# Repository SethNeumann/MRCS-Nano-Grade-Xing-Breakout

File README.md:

# REPO NAME: MRCS-Nano-Grade-Xing-Breakout

## License: Creative Commons Attribution-NonCommercial-ShareAlike

There are plenty of good Arduino Grade Xing sketches. This board supports one by Jon Schmidt which uses the Nano's 8
analog inputs to monitor up 4 sets of sensors. It drives 2 servos for the crossing gates, 2 phases of LEDs
for the flashing lights and an output to drive a crossing bell sound module, like the ones from our friends
at Iowa Scaled Engineering.

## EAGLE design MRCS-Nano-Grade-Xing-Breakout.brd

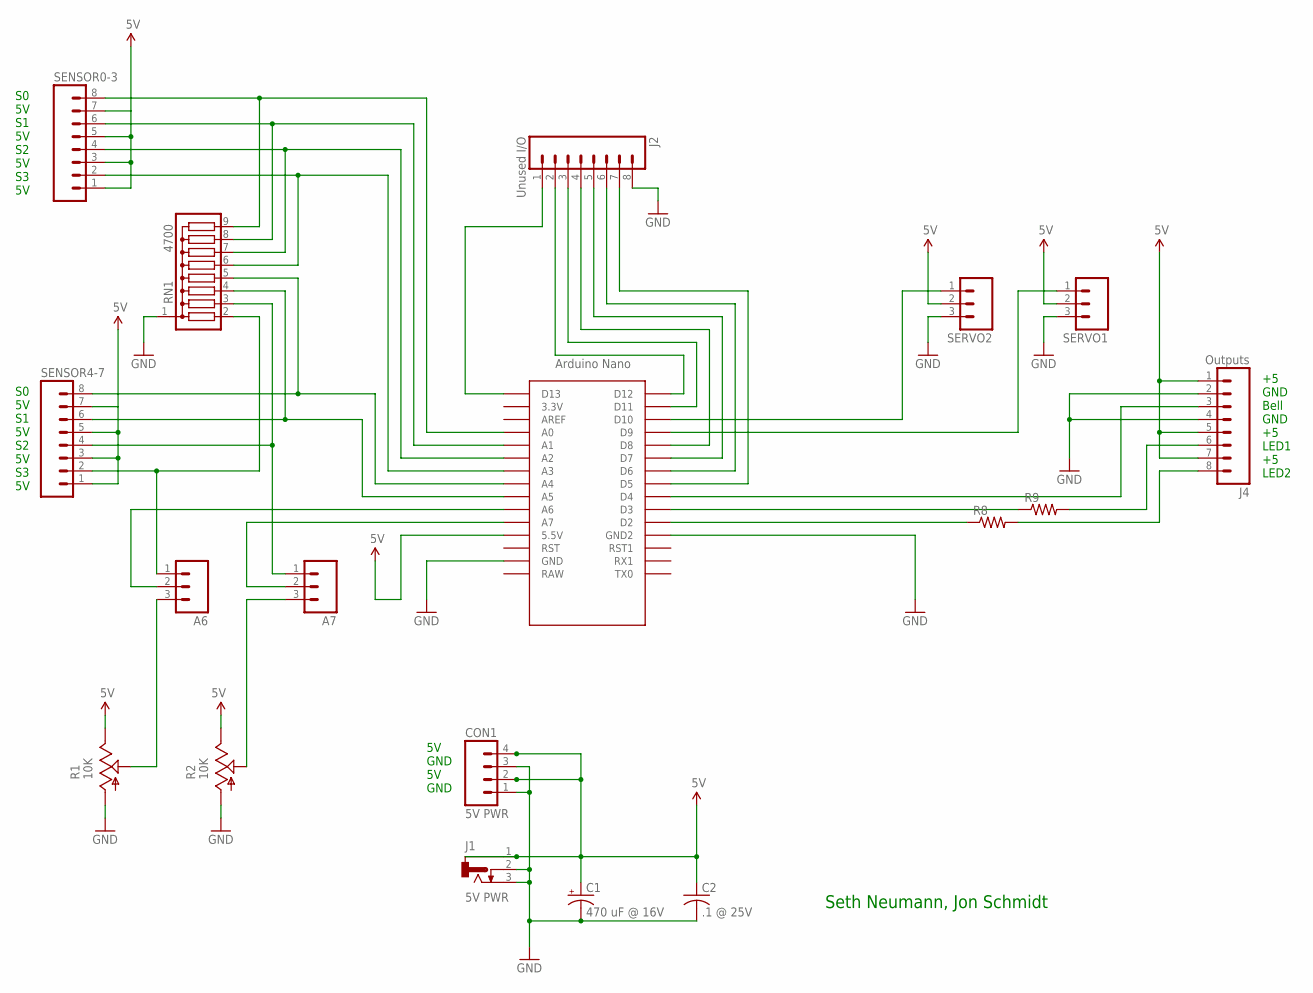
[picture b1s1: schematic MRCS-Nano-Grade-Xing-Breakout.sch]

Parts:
A6, A7: M03LOCK; 1X03_LOCK
C1: 470 uF @ 16V; E3.5-10
C2: .1 @ 25V; C-PTH-0.100
CON1: 5V PWR; SCREWTERMINAL-3.5MM-4_LOCK
J1: 5V PWR; DCJ0202
J2: Unused I/O; 1X08_LOCK
J4: Outputs; 1X08_LOCK
R1, R2: 10K; RS3
R8, R9: RPTH-R0; CUT-R
RN1: 4700; SIL9
SENSOR0-3, SENSOR4-7: CONNECTOR-M08LOCK; 1X08_LOCK
SERVO1, SERVO2: M03LOCK; 1X03_LOCK
U$1: NANO

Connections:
5V: C1.+, C2.1, CON1.2, CON1.4, J1.1, J4.1, J4.5, J4.7, R1.E, R2.E, SENSOR0-3.1, SENSOR0-3.3, SENSOR0-3.5, SENSOR0-3.7, SENSOR4-7.1, SENSOR4-7.3, SENSOR4-7.5, SENSOR4-7.7, SERVO1.2, SERVO2.2, U$1.5V (5.5V)
A0: RN1.9, SENSOR0-3.8, U$1.A0
GND: C1.-, C2.2, CON1.1, CON1.3, J1.2, J1.3, J2.8, J4.2, J4.4, R1.A, R2.A, RN1.1, SERVO1.3, SERVO2.3, U$1.GND, U$1.GND1 (GND2)
unnamed: RN1.5, SENSOR4-7.8, U$1.A4
unnamed: R8.P2 (1), U$1.D2
unnamed: J4.8, R8.P1 (2)
unnamed: R9.P2 (1), U$1.D3
unnamed: J4.6, R9.P1 (2)
unnamed: J4.3, U$1.D4
unnamed: RN1.4, SENSOR4-7.6, U$1.A5
unnamed: SERVO2.1, U$1.D10
unnamed: SERVO1.1, U$1.D9
unnamed: RN1.7, SENSOR0-3.4, U$1.A2
unnamed: A7.1, RN1.3, SENSOR4-7.4
unnamed: RN1.6, SENSOR0-3.2, U$1.A3
unnamed: A6.1, RN1.2, SENSOR4-7.2
unnamed: A6.3, R1.S
unnamed: A6.2, U$1.A6
unnamed: A7.2, U$1.A7
unnamed: RN1.8, SENSOR0-3.6, U$1.A1
unnamed: A7.3, R2.S
unnamed: J2.1, U$1.D13
unnamed: J2.2, U$1.D12
unnamed: J2.3, U$1.D11
unnamed: J2.4, U$1.D8
unnamed: J2.5, U$1.D7
unnamed: J2.6, U$1.D6
unnamed: J2.7, U$1.D5

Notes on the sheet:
5V GND 5V GND
Seth Neumann, Jon Schmidt
S0 5V S1 5V S2 5V S3 5V
+5 GND Bell GND +5 LED1 +5 LED2

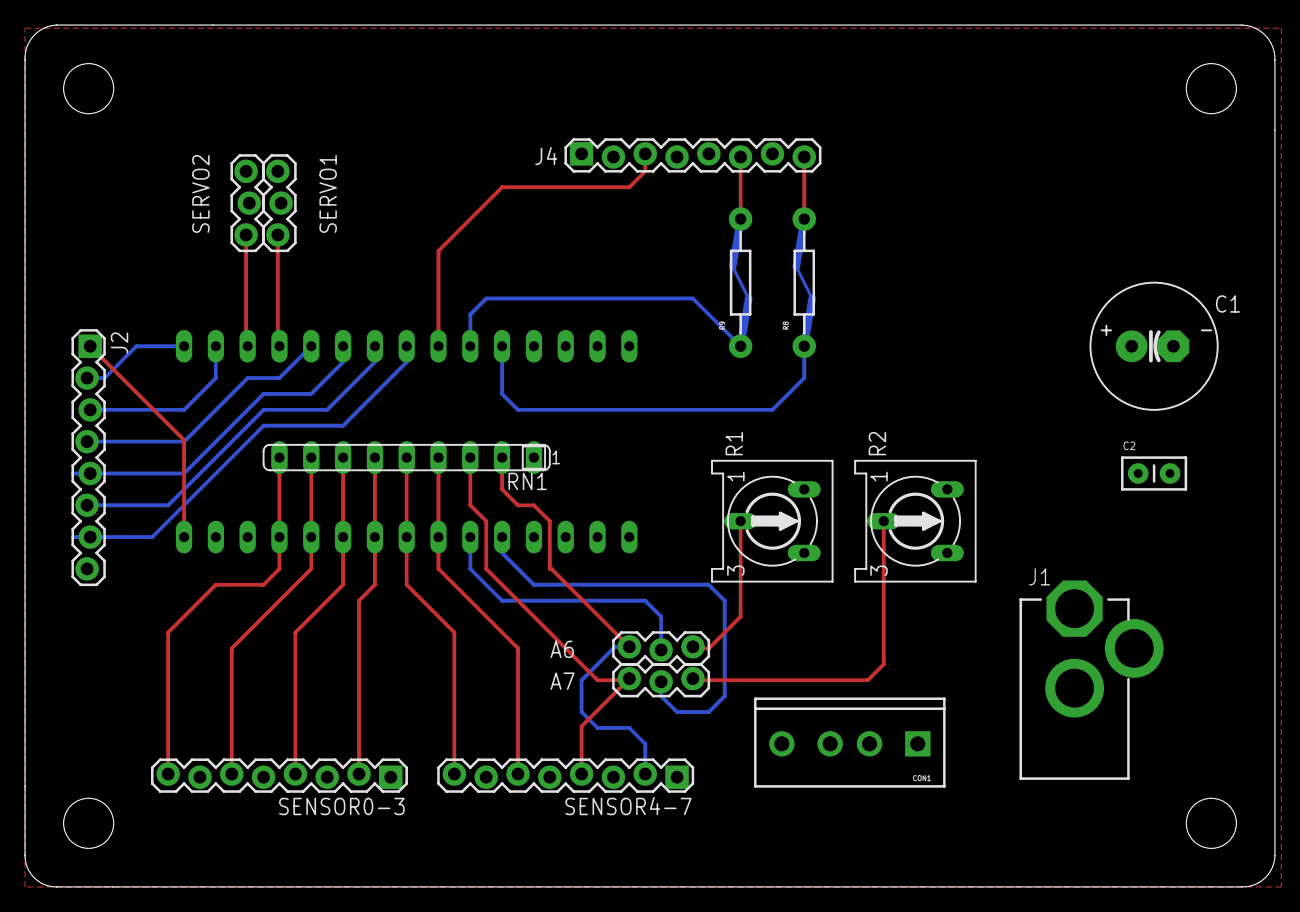
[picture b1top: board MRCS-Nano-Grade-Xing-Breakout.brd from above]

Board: 2 copper layers, 99.8 x 68.8 mm, 21 parts (0 on the bottom side), 28 nets.

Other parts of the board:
U$2: CA-PROP65WARNING
U$3: MRCSLOGOTOP
U$10: BOARD-DINRAIL-2.7IN

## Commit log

2022-03-12 initial commit
    started from the PCR Clinic board
2022-03-15 completed initial deisgn
    After some consultation with Jon Schmidt this is ready to try for fab
2022-03-16 fixed a few labels per Jon S
2022-03-30 gerb files for first build
2022-03-30 relects first board
2022-04-16 after first build
2022-04-16 update to production status
2022-04-16 clean up for listing product on site
    removed individual gerb files, use the zip
    added pdf of BOM
2022-05-07 cleanup of minor issues mostly A6 A7 jumpers
    these allow you to use either on board pots to set limits for servo movement for the crossing gates or to use A6,A7 for additional sensors with pull downs. A6 and A7 were reversed, so the traces were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
2022-09-18 junk files to be removed
    old work files removed

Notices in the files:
parts and their libraries:
SparkFun-Connectors: Licensing: Creative Commons ShareAlike 4.0 International - https://creativecommons.org/licenses/by-sa/4.0
SparkFun-Aesthetics: Licensing: CC v3.0 Share-Alike You are welcome to use this library for commercial purposes.
